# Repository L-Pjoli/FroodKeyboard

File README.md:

# Frood 75% Keyboard

This repo is for a PCB made using KiCAD that, when fabricated, gives a 75% mechanical keyboard that works with the [Frood microcontroller from 42 keebs](https://42keebs.eu/shop/parts/controllers/frood-rp2040-pro-micro-controller/).
The correct export files are located in the Gerber Export zip folder.

This keyboard follows a layout of 75%, with 81 keys and a EC11 rotary encoder. 

Front-View of the Keyboard PCB

Back View of the Keyboard PCB

The 3d-printable case is currently a WIP. I will update this repo when it is done.

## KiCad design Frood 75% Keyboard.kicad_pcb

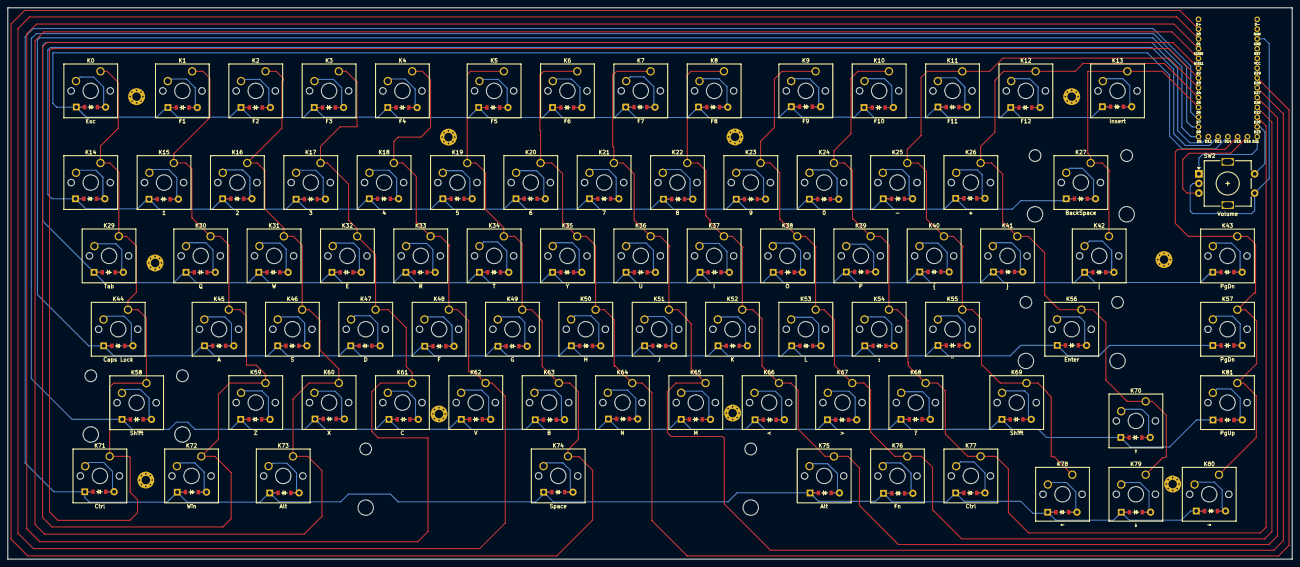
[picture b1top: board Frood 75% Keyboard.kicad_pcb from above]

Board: 2 copper layers, 333.6 x 143.2 mm, 174 parts (0 on the bottom side), 106 nets.

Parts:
D0, D1, D2, D3, D4, D5, D6, D7, D8, D9, D10, D11, D12, D13, D14, D15, D16, D17, D18, D19, D20, D21, D22, D23, D24, D25, D26, D27, D29, D30, D31, D32, D33, D34, D35, D36, D37, D38, D39, D40, D41, D42, D43, D44, D45, D46, D47, D48, D49, D50, D51, D52, D53, D54, D55, D56, D57, D58, D59, D60, D61, D62, D63, D64, D65, D66, D67, D68, D69, D70, D71, D72, D73, D74, D75, D76, D77, D78, D79, D80, D81: ComboDiode
K0: Esc; SW_Cherry_MX_1.00u_PCB
K1: F1; SW_Cherry_MX_1.00u_PCB
K2: F2; SW_Cherry_MX_1.00u_PCB
K3: F3; SW_Cherry_MX_1.00u_PCB
K4: F4; SW_Cherry_MX_1.00u_PCB
K5: F5; SW_Cherry_MX_1.00u_PCB
K6: F6; SW_Cherry_MX_1.00u_PCB
K7: F7; SW_Cherry_MX_1.00u_PCB
K8: F8; SW_Cherry_MX_1.00u_PCB
K9: F9; SW_Cherry_MX_1.00u_PCB
K10: F10; SW_Cherry_MX_1.00u_PCB
K11: F11; SW_Cherry_MX_1.00u_PCB
K12: F12; SW_Cherry_MX_1.00u_PCB
K13: Insert; SW_Cherry_MX_1.00u_PCB
K14: SW_Cherry_MX_1.00u_PCB
K15: 1; SW_Cherry_MX_1.00u_PCB
K16: 2; SW_Cherry_MX_1.00u_PCB
K17: 3; SW_Cherry_MX_1.00u_PCB
K18: 4; SW_Cherry_MX_1.00u_PCB
K19: 5; SW_Cherry_MX_1.00u_PCB
K20: 6; SW_Cherry_MX_1.00u_PCB
K21: 7; SW_Cherry_MX_1.00u_PCB
K22: 8; SW_Cherry_MX_1.00u_PCB
K23: 9; SW_Cherry_MX_1.00u_PCB
K24: 0; SW_Cherry_MX_1.00u_PCB
K25: -; SW_Cherry_MX_1.00u_PCB
K26: +; SW_Cherry_MX_1.00u_PCB
K27: BackSpace; SW_Cherry_MX_2.00u_PCB
K29: Tab; SW_Cherry_MX_1.50u_PCB
K30: Q; SW_Cherry_MX_1.00u_PCB
K31: W; SW_Cherry_MX_1.00u_PCB
K32: E; SW_Cherry_MX_1.00u_PCB
K33: R; SW_Cherry_MX_1.00u_PCB
K34: T; SW_Cherry_MX_1.00u_PCB
K35: Y; SW_Cherry_MX_1.00u_PCB
K36: U; SW_Cherry_MX_1.00u_PCB
K37: I; SW_Cherry_MX_1.00u_PCB
K38: O; SW_Cherry_MX_1.00u_PCB
K39: P; SW_Cherry_MX_1.00u_PCB
K40: {; SW_Cherry_MX_1.00u_PCB
K41: }; SW_Cherry_MX_1.00u_PCB
K42: |; SW_Cherry_MX_1.50u_PCB
K43, K57: PgDn; SW_Cherry_MX_1.00u_PCB
K44: Caps Lock; SW_Cherry_MX_1.75u_PCB
K45: A; SW_Cherry_MX_1.00u_PCB
K46: S; SW_Cherry_MX_1.00u_PCB
K47: D; SW_Cherry_MX_1.00u_PCB
K48: F; SW_Cherry_MX_1.00u_PCB
K49: G; SW_Cherry_MX_1.00u_PCB
K50: H; SW_Cherry_MX_1.00u_PCB
K51: J; SW_Cherry_MX_1.00u_PCB
K52: K; SW_Cherry_MX_1.00u_PCB
K53: L; SW_Cherry_MX_1.00u_PCB
K54: :; SW_Cherry_MX_1.00u_PCB
K55: "; SW_Cherry_MX_1.00u_PCB
K56: Enter; SW_Cherry_MX_2.25u_PCB
K58: Shift; SW_Cherry_MX_2.25u_PCB
K59: Z; SW_Cherry_MX_1.00u_PCB
K60: X; SW_Cherry_MX_1.00u_PCB
K61: C; SW_Cherry_MX_1.00u_PCB
K62: V; SW_Cherry_MX_1.00u_PCB
K63: B; SW_Cherry_MX_1.00u_PCB
K64: N; SW_Cherry_MX_1.00u_PCB
K65: M; SW_Cherry_MX_1.00u_PCB
K66: <; SW_Cherry_MX_1.00u_PCB
K67: >; SW_Cherry_MX_1.00u_PCB
K68: ?; SW_Cherry_MX_1.00u_PCB
K69: Shift; SW_Cherry_MX_1.75u_PCB
K70: ↑; SW_Cherry_MX_1.00u_PCB
K71: Ctrl; SW_Cherry_MX_1.25u_PCB
K72: Win; SW_Cherry_MX_1.25u_PCB
K73: Alt; SW_Cherry_MX_1.25u_PCB
K74: Space; SW_Cherry_MX_6.25u_PCB
K75: Alt; SW_Cherry_MX_1.00u_PCB
K76: Fn; SW_Cherry_MX_1.00u_PCB
K77: Ctrl; SW_Cherry_MX_1.00u_PCB
K78: ←; SW_Cherry_MX_1.00u_PCB
K79: ↓; SW_Cherry_MX_1.00u_PCB
K80: →; SW_Cherry_MX_1.00u_PCB
K81: PgUp; SW_Cherry_MX_1.00u_PCB
SW2: Volume; RotaryEncoder_Alps_EC11E-Switch_Vertical_H20mm
U1: Frood; PinHeader_2x13+5_P2.54mm_Vertical_Frood
_5, _5#2, _5#3, _5#4, _5#5, _5#6, _5#7, _5#8, _5#9, _5#10: MountingHole_2.2mm_M2_Pad_Via

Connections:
/Col_0: K0.1, K14.1, K29.1, K44.1, K58.1, K71.1, U1.7 (D3)
/Col_1: K1.1, K15.1, K30.1, K45.1, K59.1, K72.1, U1.6 (D2)
/Col_2: K2.1, K16.1, K31.1, K46.1, K60.1, K73.1, U1.5 (GND)
/Col_3: K3.1, K17.1, K32.1, K47.1, K61.1, U1.4 (GND)
/Col_4: K4.1, K18.1, K33.1, K48.1, K62.1, U1.3 (D1)
/Col_5: K5.1, K19.1, K34.1, K49.1, K63.1, K74.1, U1.2 (D0)
/Col_6: K6.1, K20.1, K35.1, K50.1, K64.1, U1.25 (D28/A2)
/Col_7: K7.1, K21.1, K36.1, K51.1, K65.1, U1.24 (D27/A1)
/Col_8: K8.1, K22.1, K37.1, K52.1, K66.1, K75.1, U1.23 (D26/A0)
/Col_9: K9.1, K23.1, K38.1, K53.1, K67.1, K76.1, U1.22 (D22)
/Col_10: K10.1, K24.1, K39.1, K54.1, K68.1, K77.1, U1.21 (D20)
/Col_11: K11.1, K25.1, K40.1, K55.1, K69.1, K78.1, U1.8 (D4)
/Col_12: K12.1, K26.1, K41.1, K56.1, K70.1, K79.1, U1.9 (D5)
/Col_13: K13.1, K27.1, K42.1, U1.10 (D6)
/Row_0: D71.1, D72.1, D73.1, D74.1, D75.1, D76.1, D77.1, D78.1, D79.1, D80.1, U1.11 (D7)
/Row_1: D58.1, D59.1, D60.1, D61.1, D62.1, D63.1, D64.1, D65.1, D66.1, D67.1, D68.1, D69.1, D70.1, D81.1, U1.12 (D8)
/Row_2: D44.1, D45.1, D46.1, D47.1, D48.1, D49.1, D50.1, D51.1, D52.1, D53.1, D54.1, D55.1, D56.1, D57.1, U1.13 (D9)
/Row_3: D29.1, D30.1, D31.1, D32.1, D33.1, D34.1, D35.1, D36.1, D37.1, D38.1, D39.1, D40.1, D41.1, D42.1, D43.1, U1.14 (D12)
/Row_4: D14.1, D15.1, D16.1, D17.1, D18.1, D19.1, D20.1, D21.1, D22.1, D23.1, D24.1, D25.1, D26.1, D27.1, U1.15 (D13)
/Row_5: D0.1, D1.1, D2.1, D3.1, D4.1, D5.1, D6.1, D7.1, D8.1, D9.1, D10.1, D11.1, D12.1, D13.1, U1.16 (D14)
Col-14: K43.1, K57.1, K80.1, K81.1, U1.17 (D15)
unnamed: D0.2, K0.2
unnamed: D1.2, K1.2
unnamed: D2.2, K2.2
unnamed: D3.2, K3.2
unnamed: D4.2, K4.2
unnamed: D5.2, K5.2
unnamed: D6.2, K6.2
unnamed: D7.2, K7.2
unnamed: D8.2, K8.2
unnamed: D9.2, K9.2
unnamed: D10.2, K10.2
unnamed: D11.2, K11.2
unnamed: D12.2, K12.2
unnamed: D13.2, K13.2
unnamed: D14.2, K14.2
unnamed: D15.2, K15.2
unnamed: D16.2, K16.2
unnamed: D17.2, K17.2
unnamed: D18.2, K18.2
unnamed: D19.2, K19.2
unnamed: D20.2, K20.2
unnamed: D21.2, K21.2
unnamed: D22.2, K22.2
unnamed: D23.2, K23.2
unnamed: D24.2, K24.2
unnamed: D25.2, K25.2
unnamed: D26.2, K26.2
unnamed: D27.2, K27.2
unnamed: D29.2, K29.2
unnamed: D30.2, K30.2
unnamed: D31.2, K31.2
unnamed: D32.2, K32.2
unnamed: D33.2, K33.2
unnamed: D34.2, K34.2
unnamed: D35.2, K35.2
unnamed: D36.2, K36.2
unnamed: D37.2, K37.2
unnamed: D38.2, K38.2
unnamed: D39.2, K39.2
unnamed: D40.2, K40.2
unnamed: D41.2, K41.2
unnamed: D42.2, K42.2
unnamed: D81.2, K81.2
unnamed: D44.2, K44.2
unnamed: D45.2, K45.2
unnamed: D46.2, K46.2
unnamed: D47.2, K47.2
unnamed: D48.2, K48.2
unnamed: D49.2, K49.2
unnamed: D50.2, K50.2
unnamed: D51.2, K51.2
unnamed: D52.2, K52.2
unnamed: D53.2, K53.2
unnamed: D54.2, K54.2
unnamed: D55.2, K55.2
unnamed: D56.2, K56.2
unnamed: D57.2, K57.2
unnamed: D58.2, K58.2
unnamed: D59.2, K59.2
unnamed: D60.2, K60.2
unnamed: D61.2, K61.2
unnamed: D62.2, K62.2
unnamed: D63.2, K63.2
unnamed: D64.2, K64.2
unnamed: D65.2, K65.2
unnamed: D66.2, K66.2
unnamed: D67.2, K67.2
unnamed: D68.2, K68.2
unnamed: D69.2, K69.2
unnamed: D70.2, K70.2
unnamed: D71.2, K71.2
unnamed: D72.2, K72.2
unnamed: D73.2, K73.2
unnamed: D74.2, K74.2
unnamed: D75.2, K75.2
unnamed: D76.2, K76.2
unnamed: D77.2, K77.2
unnamed: D78.2, K78.2
unnamed: D79.2, K79.2
unnamed: D80.2, K80.2
unnamed: D43.2, K43.2
Net-Rotary-GND-1: SW2.C, SW2.S1, U1.29 (GND)
Net-Rotary_A: SW2.A, U1.19 (D21)
Net-Rotary_B: SW2.B, U1.18 (D16)
Net-Rotary_C: SW2.S2, U1.20 (D23)

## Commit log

2024-10-16 PCB Done
2024-10-16 readme
